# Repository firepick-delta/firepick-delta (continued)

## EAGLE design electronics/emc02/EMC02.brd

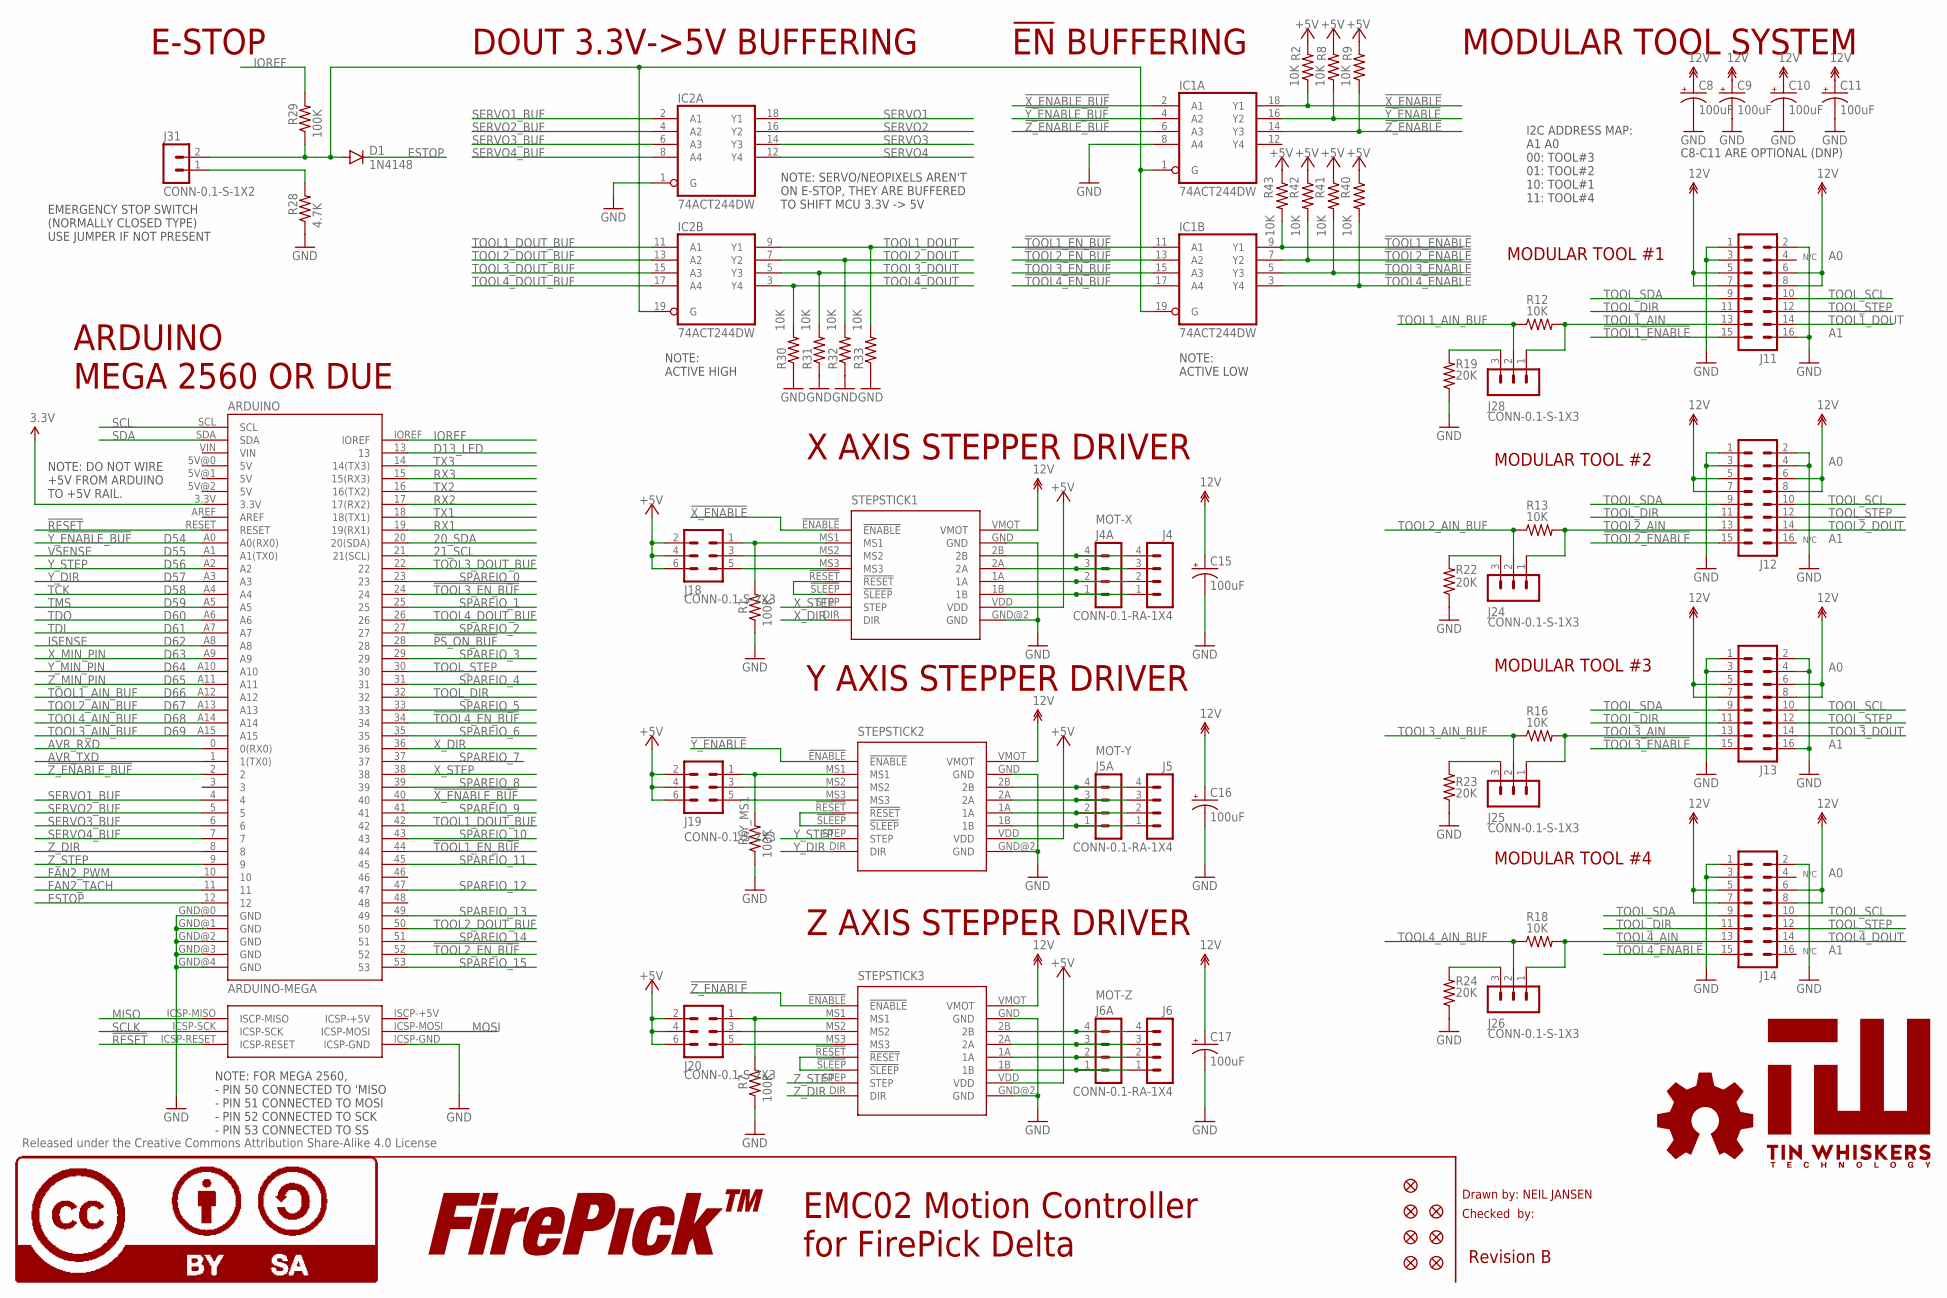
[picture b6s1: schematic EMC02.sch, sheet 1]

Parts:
ARDUINO: ARDUINO-MEGA; PARTNO CONN-0.1-ARD-2560
C8, C9, C10, C11, C15, C16, C17: 100uF; PANASONIC_D; PARTNO 25TXV100M6.3X8
D1: 1N4148; SOD-123; PARTNO 1N4148W-7-F
FID1, FID2, FID3, FID4, FID5, FID6, FID7: FIDUCIAL
IC1, IC2: 74ACT244DW; SO20W; PARTNO 74ACT244SCX
J4, J5, J6: CONN-0.1-RA-1X4; MA04-1; PARTNO CONN-0.1-RA-1X4
J4A: MOT-X; CONN-JST-PH_2.0MM_4PIN-SMT-RA
J5A: MOT-Y; CONN-JST-PH_2.0MM_4PIN-SMT-RA
J6A: MOT-Z; CONN-JST-PH_2.0MM_4PIN-SMT-RA
J11, J12, J13, J14: CONN-RECT-16PIN-2ROW; CONN-RECT-2.54MM-16PIN-2ROW-SMTH; PARTNO PPPC081LFBN-RC
J18, J19, J20: CONN-0.1-S-2X3; MA03-2; PARTNO CONN-0.1-S-2X3
J24, J25, J26, J28: CONN-0.1-S-1X3; MA03-1; PARTNO CONN-0.1-S-1X3
J31: CONN-0.1-S-1X2; MA02-1; PARTNO CONN-0.1-S-1X2
LOGO4: LOGO-FIREPICKLARGE; LOGO-FIREPICK
LOGO5: LOGO-OSHWMEDIUM; LOGO-OSHW-MEDIUM
LOGO6: LOGO-CC-BY-SALARGE; LOGO-CC-BY-SA
R1, R6, R7, R29: 100K; 0805; PARTNO RC0805FR-07100KL
R2, R8, R9, R12, R13, R16, R18, R30, R31, R32, R33, R40, R41, R42, R43: 10K; 0805; PARTNO RC0805FR-0710KL
R19, R22, R23, R24: 20K; 0805; PARTNO RC0805FR-0720KL
R28: 4.7K; 0805; PARTNO RC0805FR-074K7L
STEPSTICK1, STEPSTICK2, STEPSTICK3: STEPSTICK; PARTNO PPPC081LFBN-RC
U$25: TIN-WHISKERSTSTOP; TIN-WHISKERS-TSTOP

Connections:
3.3V: ARDUINO.3.3V; also elsewhere on the board
12V: C8.+, C9.+, C10.+, C11.+, C15.+, C16.+, C17.+, J11.5, J11.6, J11.7, J11.8, J12.5, J12.6, J12.7, J12.8, J13.5, J13.6, J13.7, J13.8, J14.5, J14.6, J14.7, J14.8, STEPSTICK1.VMOT, STEPSTICK2.VMOT, STEPSTICK3.VMOT; also elsewhere on the board
20_SDA: ARDUINO.20 (20(SDA)); also elsewhere on the board
21_SCL: ARDUINO.21 (21(SCL)); also elsewhere on the board
!PS_ON_BUF: ARDUINO.28; also elsewhere on the board
!RESET: ARDUINO.ICSP-RESET, ARDUINO.RESET; also elsewhere on the board
!TOOL1_ENABLE: IC1.9 (Y1), J11.15, R43.2
!TOOL1_EN_BUF: ARDUINO.44, IC1.11 (A1)
!TOOL2_ENABLE: IC1.7 (Y2), J12.15, R42.2
!TOOL2_EN_BUF: ARDUINO.52, IC1.13 (A2)
!TOOL3_ENABLE: IC1.5 (Y3), J13.15, R41.2
!TOOL3_EN_BUF: ARDUINO.24, IC1.15 (A3)
!TOOL4_ENABLE: IC1.3 (Y4), J14.15, R40.2
!TOOL4_EN_BUF: ARDUINO.34, IC1.17 (A4)
!X_ENABLE: IC1.18 (Y1), R2.1, STEPSTICK1.!ENABLE!
!X_ENABLE_BUF: ARDUINO.40, IC1.2 (A1)
!Y_ENABLE: IC1.16 (Y2), R8.1, STEPSTICK2.!ENABLE!
!Y_ENABLE_BUF: ARDUINO.A0 (A0(RX0)), IC1.4 (A2)
!Z_ENABLE: IC1.14 (Y3), R9.1, STEPSTICK3.!ENABLE!
!Z_ENABLE_BUF: ARDUINO.2, IC1.6 (A3)
+5V: J18.2, J18.4, J18.6, J19.2, J19.4, J19.6, J20.2, J20.4, J20.6, R2.2, R8.2, R9.2, R40.1, R41.1, R42.1, R43.1, STEPSTICK1.VDD, STEPSTICK2.VDD, STEPSTICK3.VDD; also elsewhere on the board
AVR_RXD: ARDUINO.0 (0(RX0)); also elsewhere on the board
AVR_TXD: ARDUINO.1 (1(TX0)); also elsewhere on the board
D13_LED: ARDUINO.13; also elsewhere on the board
ESTOP: ARDUINO.12, D1.C
ESTOP_OE: D1.A, IC1.1 (G), IC1.19 (G), IC2.19 (G), J31.2, R29.1
FAN2_PWM: ARDUINO.10; also elsewhere on the board
FAN2_TACH: ARDUINO.11; also elsewhere on the board
GND: ARDUINO.GND@0 (GND), ARDUINO.GND@1 (GND), ARDUINO.GND@2 (GND), ARDUINO.GND@3 (GND), ARDUINO.GND@4 (GND), ARDUINO.ICSP-GND, C8.-, C9.-, C10.-, C11.-, C15.-, C16.-, C17.-, IC1.8 (A4), IC2.1 (G), J11.1, J11.2, J11.3, J11.16, J12.1, J12.2, J12.3, J12.4, J13.1, J13.2, J13.3, J13.4, J13.16, J14.1, J14.2, J14.3, R1.1, R6.1, R7.1, R19.1, R22.1, R23.1, R24.1, R28.1, R30.1, R31.1, R32.1, R33.1, STEPSTICK1.GND, STEPSTICK1.GND@2 (GND), STEPSTICK2.GND, STEPSTICK2.GND@2 (GND), STEPSTICK3.GND, STEPSTICK3.GND@2 (GND); also elsewhere on the board
IOREF: ARDUINO.IOREF, R29.2; also elsewhere on the board
ISENSE: ARDUINO.A8; also elsewhere on the board
MISO: ARDUINO.ICSP-MISO (ISCP-MISO); also elsewhere on the board
MOSI: ARDUINO.ICSP-MOSI; also elsewhere on the board
unnamed: J31.1, R28.2
unnamed: J24.3, R22.2
unnamed: J28.3, R19.2
unnamed: STEPSTICK1.!RESET!, STEPSTICK1.!SLEEP!
unnamed: J25.3, R23.2
unnamed: J26.3, R24.2
unnamed: STEPSTICK2.!RESET!, STEPSTICK2.!SLEEP!
unnamed: STEPSTICK3.!RESET!, STEPSTICK3.!SLEEP!
RX1: ARDUINO.19 (19(RX1)); also elsewhere on the board
RX2: ARDUINO.17 (17(RX2)); also elsewhere on the board
RX3: ARDUINO.15 (15(RX3)); also elsewhere on the board
SCL: ARDUINO.SCL; also elsewhere on the board
SCLK: ARDUINO.ICSP-SCK; also elsewhere on the board
SDA: ARDUINO.SDA; also elsewhere on the board
SERVO1: IC2.18 (Y1); also elsewhere on the board
SERVO1_BUF: ARDUINO.4, IC2.2 (A1)
SERVO2: IC2.16 (Y2); also elsewhere on the board
SERVO2_BUF: ARDUINO.5, IC2.4 (A2)
SERVO3: IC2.14 (Y3); also elsewhere on the board
SERVO3_BUF: ARDUINO.6, IC2.6 (A3)
SERVO4: IC2.12 (Y4); also elsewhere on the board
SERVO4_BUF: ARDUINO.7, IC2.8 (A4)
SPAREIO_0: ARDUINO.23; also elsewhere on the board
SPAREIO_1: ARDUINO.25; also elsewhere on the board
SPAREIO_2: ARDUINO.27; also elsewhere on the board
SPAREIO_3: ARDUINO.29; also elsewhere on the board
SPAREIO_4: ARDUINO.31; also elsewhere on the board
SPAREIO_5: ARDUINO.33; also elsewhere on the board
SPAREIO_6: ARDUINO.35; also elsewhere on the board
SPAREIO_7: ARDUINO.37; also elsewhere on the board
SPAREIO_8: ARDUINO.39; also elsewhere on the board
SPAREIO_9: ARDUINO.41; also elsewhere on the board
SPAREIO_10: ARDUINO.43; also elsewhere on the board
SPAREIO_11: ARDUINO.45; also elsewhere on the board
SPAREIO_12: ARDUINO.47; also elsewhere on the board
SPAREIO_13: ARDUINO.49; also elsewhere on the board
SPAREIO_14: ARDUINO.51; also elsewhere on the board
SPAREIO_15: ARDUINO.53; also elsewhere on the board
TCK: ARDUINO.A4; also elsewhere on the board
TDI: ARDUINO.A7; also elsewhere on the board
TDO: ARDUINO.A6; also elsewhere on the board
TMS: ARDUINO.A5; also elsewhere on the board
TOOL1_AIN: J11.13, J28.1, R12.2
TOOL1_AIN_BUF: ARDUINO.A12, J28.2, R12.1
TOOL1_DOUT: IC2.9 (Y1), J11.14, R33.2
TOOL1_DOUT_BUF: ARDUINO.42, IC2.11 (A1)
TOOL2_AIN: J12.13, J24.1, R13.2
TOOL2_AIN_BUF: ARDUINO.A13, J24.2, R13.1
TOOL2_DOUT: IC2.7 (Y2), J12.14, R32.2
TOOL2_DOUT_BUF: ARDUINO.50, IC2.13 (A2)
TOOL3_AIN: J13.13, J25.1, R16.2
TOOL3_AIN_BUF: ARDUINO.A15, J25.2, R16.1
TOOL3_DOUT: IC2.5 (Y3), J13.14, R31.2
TOOL3_DOUT_BUF: ARDUINO.22, IC2.15 (A3)
TOOL4_AIN: J14.13, J26.1, R18.2
TOOL4_AIN_BUF: ARDUINO.A14, J26.2, R18.1
TOOL4_DOUT: IC2.3 (Y4), J14.14, R30.2
TOOL4_DOUT_BUF: ARDUINO.26, IC2.17 (A4)
TOOL_DIR: ARDUINO.32, J11.11, J12.11, J13.11, J14.11
TOOL_SCL: J11.10, J12.10, J13.10, J14.10; also elsewhere on the board
TOOL_SDA: J11.9, J12.9, J13.9, J14.9; also elsewhere on the board
TOOL_STEP: ARDUINO.30, J11.12, J12.12, J13.12, J14.12
TX1: ARDUINO.18 (18(TX1)); also elsewhere on the board
TX2: ARDUINO.16 (16(TX2)); also elsewhere on the board
TX3: ARDUINO.14 (14(TX3)); also elsewhere on the board
VSENSE: ARDUINO.A1 (A1(TX0)); also elsewhere on the board
X1A: J4.2, J4A.2, STEPSTICK1.1A
X1B: J4.1, J4A.1, STEPSTICK1.1B
X2A: J4.3, J4A.3, STEPSTICK1.2A
X2B: J4.4, J4A.4, STEPSTICK1.2B
X_DIR: ARDUINO.36, STEPSTICK1.DIR
X_MIN_PIN: ARDUINO.A9; also elsewhere on the board
X_MS1: J18.1, R1.2, STEPSTICK1.MS1
X_MS2: J18.3, STEPSTICK1.MS2
X_MS3: J18.5, STEPSTICK1.MS3
X_STEP: ARDUINO.38, STEPSTICK1.STEP
Y1A: J5.2, J5A.2, STEPSTICK2.1A
Y1B: J5.1, J5A.1, STEPSTICK2.1B
Y2A: J5.3, J5A.3, STEPSTICK2.2A
Y2B: J5.4, J5A.4, STEPSTICK2.2B
Y_DIR: ARDUINO.A3, STEPSTICK2.DIR
Y_MIN_PIN: ARDUINO.A10; also elsewhere on the board
Y_MS1: J19.1, R6.2, STEPSTICK2.MS1
Y_MS2: J19.3, STEPSTICK2.MS2
Y_MS3: J19.5, STEPSTICK2.MS3
Y_STEP: ARDUINO.A2, STEPSTICK2.STEP
Z1A: J6.2, J6A.2, STEPSTICK3.1A
Z1B: J6.1, J6A.1, STEPSTICK3.1B
Z2A: J6.3, J6A.3, STEPSTICK3.2A
Z2B: J6.4, J6A.4, STEPSTICK3.2B
Z_DIR: ARDUINO.8, STEPSTICK3.DIR
Z_MIN_PIN: ARDUINO.A11; also elsewhere on the board
Z_MS1: J20.1, R7.2, STEPSTICK3.MS1
Z_MS2: J20.3, STEPSTICK3.MS2
Z_MS3: J20.5, STEPSTICK3.MS3
Z_STEP: ARDUINO.9, STEPSTICK3.STEP

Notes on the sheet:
I2C ADDRESS MAP: A1 A0 00: TOOL#3 01: TOOL#2 10: TOOL#1 11: TOOL#4
MODULAR TOOL #4
MODULAR TOOL #3
MODULAR TOOL #2
MODULAR TOOL #1
Drawn by: NEIL JANSEN
Checked by:
Revision B
EMC02 Motion Controller for FirePick Delta
ARDUINO MEGA 2560 OR DUE
X AXIS STEPPER DRIVER
N/C
Y AXIS STEPPER DRIVER
Z AXIS STEPPER DRIVER
Released under the Creative Commons Attribution Share-Alike 4.0 License
D54
D55
D56
D57
D58
D59
D60
D61
D62
D63
D64
D65
D66
D67
D68
D69
NOTE: DO NOT WIRE +5V FROM ARDUINO TO +5V RAIL.
MODULAR TOOL SYSTEM
DOUT 3.3V->5V BUFFERING
EMERGENCY STOP SWITCH (NORMALLY CLOSED TYPE) USE JUMPER IF NOT PRESENT
E-STOP
!EN! BUFFERING
NOTE: ACTIVE HIGH
NOTE: ACTIVE LOW
NOTE: SERVO/NEOPIXELS AREN'T ON E-STOP, THEY ARE BUFFERED TO SHIFT MCU 3.3V -> 5V

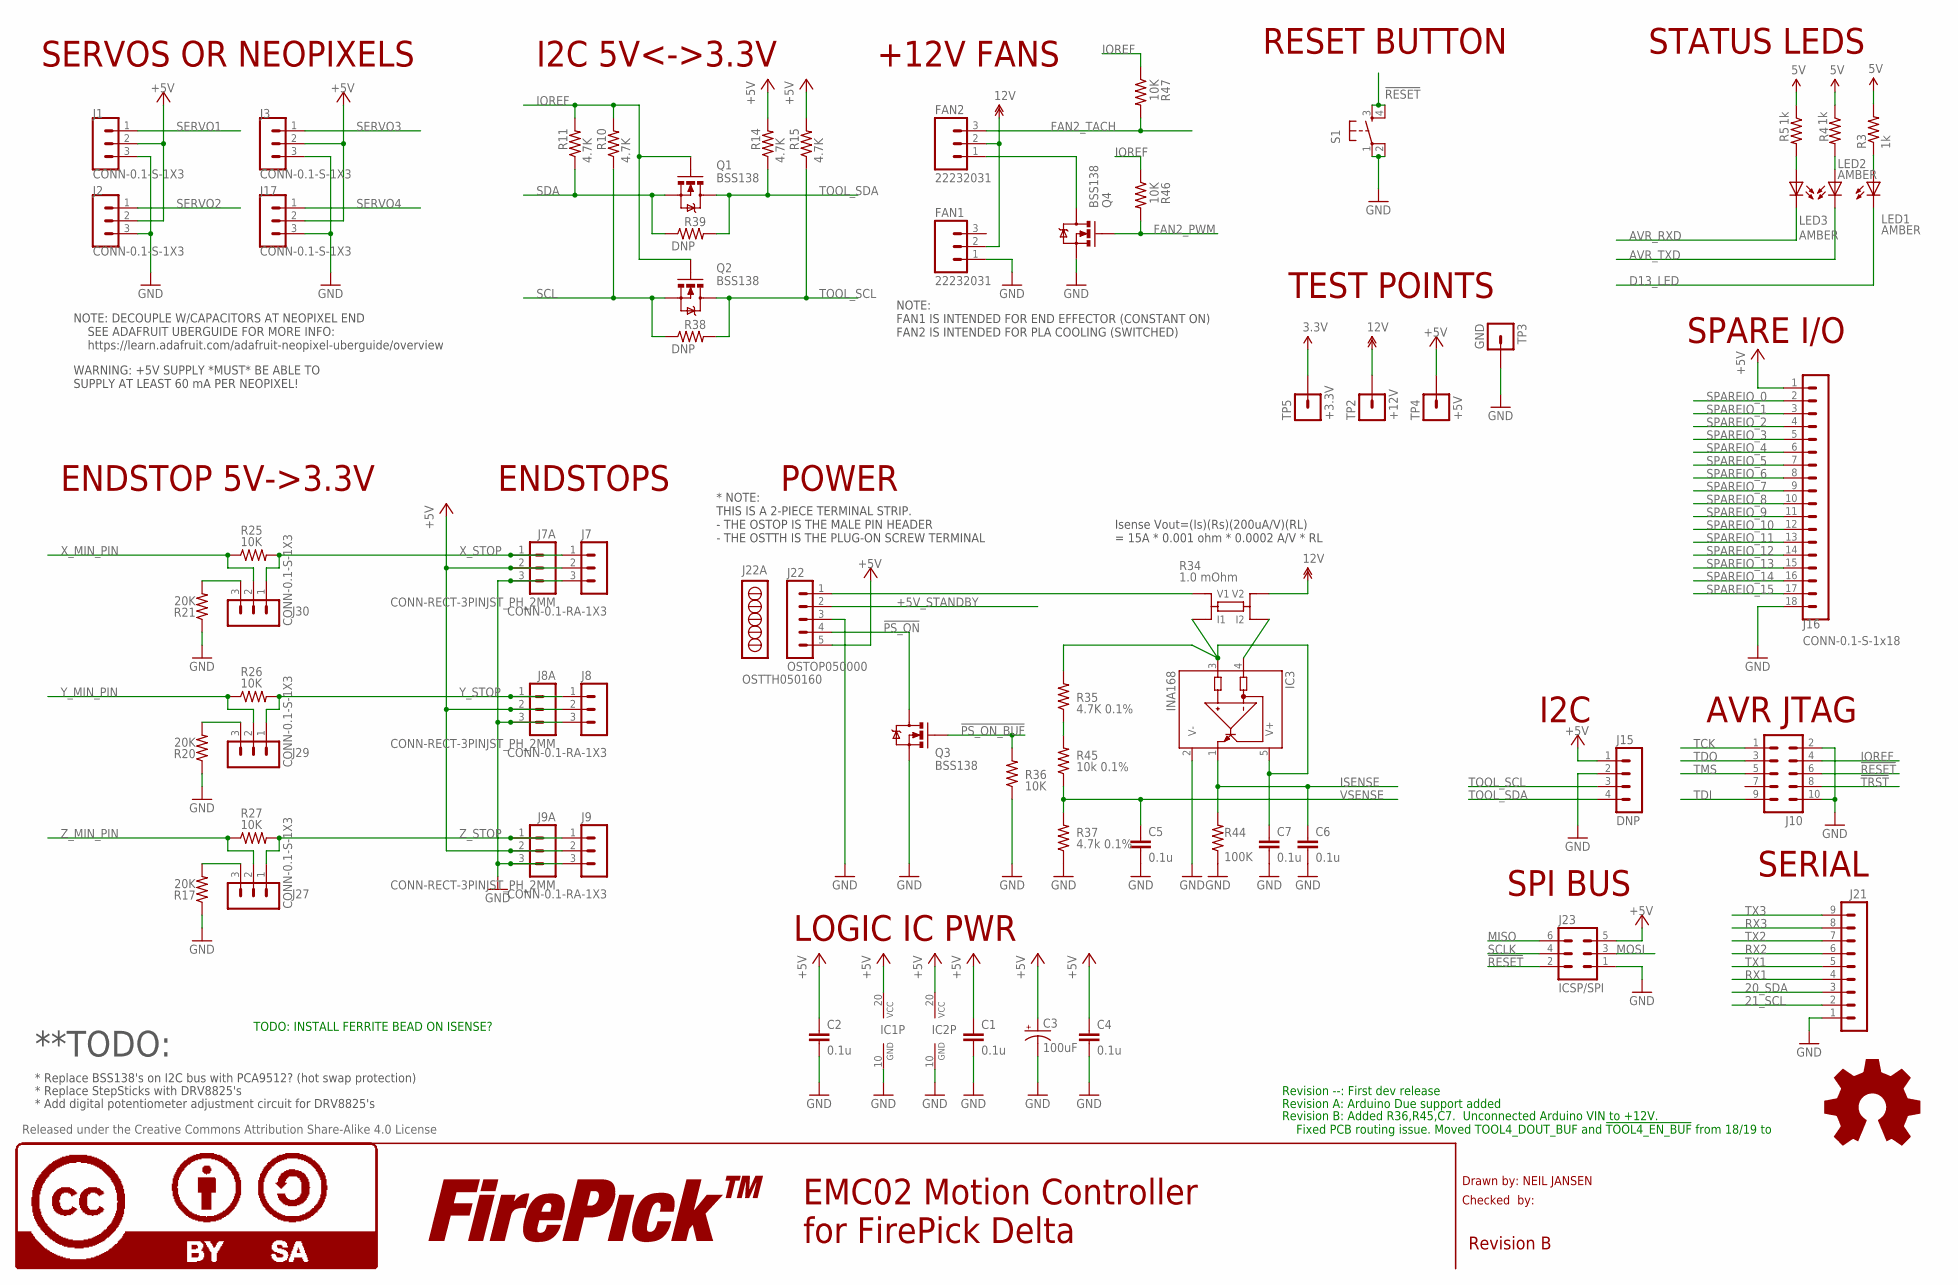
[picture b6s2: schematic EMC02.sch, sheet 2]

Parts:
C1, C2, C4, C5, C6, C7: 0.1u; 0805; PARTNO CC0805ZRY5V9BB104
C3: 100uF; PANASONIC_D; PARTNO 25TXV100M6.3X8
FAN1, FAN2: 22232031; MOLEX-1X3_LOCK; PARTNO 22232031
IC1, IC2: 74ACT244DW; SO20W; PARTNO 74ACT244SCX
IC3: INA168; SOT23-5; PARTNO INA168NA/3K
J1, J2, J3, J17, J27, J29, J30: CONN-0.1-S-1X3; MA03-1; PARTNO CONN-0.1-S-1X3
J7, J8, J9: CONN-0.1-RA-1X3; MA03-1; PARTNO CONN-0.1-RA-1X3
J7A, J8A, J9A: CONN-RECT-3PINJST_PH_2MM; CONN-JST_PH-2.0MM-3PIN-SMT-RA
J10: MA05-2
J15: DNP; MA04-1
J16: CONN-0.1-S-1x18; MA18-1
J21: MA09-1
J22: OSTOP050000; CONN-OSTOP050000; PARTNO OSTOP240000
J22A: OSTTH050160; CONN-OSTTH050160; PARTNO OSTTH050160
J23: ICSP/SPI; MA03-2
LED1, LED2, LED3: AMBER; LED-1206-NO_SILK; PARTNO LTST-C150AKT
LOGO1: LOGO-FIREPICKLARGE; LOGO-FIREPICK
LOGO2: LOGO-OSHWMEDIUM; LOGO-OSHW-MEDIUM
LOGO3: LOGO-CC-BY-SALARGE; LOGO-CC-BY-SA
Q1, Q2, Q3, Q4: BSS138; SOT23; PARTNO BSS138
R3, R4, R5: 1k; 0805; PARTNO RC0805FR-071KL
R10, R11, R14, R15: 4.7K; 0805; PARTNO RC0805FR-074K7L
R17, R20, R21: 20K; 0805; PARTNO RC0805FR-0720KL
R25, R26, R27, R36, R46, R47: 10K; 0805; PARTNO RC0805FR-0710KL
R34: 1.0 mOhm; CHIP-1224-KELVIN; PARTNO LVK25R001FER
R35: 4.7K 0.1%; 0805; PARTNO *
R37: 4.7k 0.1%; 0805; PARTNO *
R38, R39: DNP; 0805
R44: 100K; 0805; PARTNO *
R45: 10k 0.1%; 0805; PARTNO *
S1: TAC_SWITCHSMD; TACTILE_SWITCH_SMD; PARTNO SWITCH TACTILE SPST-NO 0.05A 12V
TP2: +12V; CON-TESTPOINT
TP3: GND; CON-TESTPOINT
TP4: +5V; CON-TESTPOINT
TP5: +3.3V; CON-TESTPOINT

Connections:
3.3V: TP5.1; also elsewhere on the board
12V: FAN1.2, FAN2.2, R34.V2, TP2.1; also elsewhere on the board
20_SDA: J21.3; also elsewhere on the board
21_SCL: J21.2; also elsewhere on the board
!PS_ON: J22.4, Q3.3 (D)
!PS_ON_BUF: Q3.1 (G), R36.2; also elsewhere on the board
!RESET: J10.6, J23.2, S1.3, S1.4; also elsewhere on the board
!TRST: J10.8
+5V: C1.1, C2.1, C3.+, C4.1, IC1.20 (VCC), IC2.20 (VCC), J1.2, J2.2, J3.2, J7.2, J7A.2, J8.2, J8A.2, J9.2, J9A.2, J15.1, J16.1, J17.2, J22.5, J23.5, R3.2, R4.1, R5.1, R14.2, R15.2, TP4.1; also elsewhere on the board
+5V_STANDBY: J22.2
AVR_RXD: LED3.C; also elsewhere on the board
AVR_TXD: LED2.C; also elsewhere on the board
D13_LED: LED1.C; also elsewhere on the board
FAN2_PWM: Q4.1 (G), R46.2; also elsewhere on the board
FAN2_TACH: FAN2.3, R47.2; also elsewhere on the board
GND: C1.2, C2.2, C3.-, C4.2, C5.2, C6.2, C7.2, FAN1.1, IC1.10 (GND), IC2.10 (GND), IC3.2 (V-), J1.3, J2.3, J3.3, J7.3, J7A.3, J8.3, J8A.3, J9.3, J9A.3, J10.2, J10.10, J15.2, J16.18, J17.3, J21.1, J22.3, J23.1, Q3.2 (S), Q4.2 (S), R17.1, R20.1, R21.1, R36.1, R37.1, R44.1, S1.1, S1.2, TP3.1; also elsewhere on the board
IOREF: J10.4, Q1.1 (G), Q2.1 (G), R10.2, R11.2, R46.1, R47.1; also elsewhere on the board
ISENSE: C6.1, IC3.1 (OUT), R44.2; also elsewhere on the board
MISO: J23.6; also elsewhere on the board
MOSI: J23.3; also elsewhere on the board
unnamed: R35.1, R45.2
unnamed: FAN2.1, Q4.3 (D)
unnamed: J22.1, R34.V1
unnamed: LED1.A, R3.1
unnamed: J27.3, R17.2
unnamed: J29.3, R20.2
unnamed: J30.3, R21.2
unnamed: C7.1, IC3.3 (IN+), IC3.5 (V+), R34.I1, R35.2
unnamed: IC3.4 (IN-), R34.I2
unnamed: LED2.A, R4.2
unnamed: LED3.A, R5.2
RX1: J21.4; also elsewhere on the board
RX2: J21.6; also elsewhere on the board
RX3: J21.8; also elsewhere on the board
SCL: Q2.2 (S), R10.1, R38.1; also elsewhere on the board
SCLK: J23.4; also elsewhere on the board
SDA: Q1.2 (S), R11.1, R39.1; also elsewhere on the board
SERVO1: J1.1; also elsewhere on the board
SERVO2: J2.1; also elsewhere on the board
SERVO3: J3.1; also elsewhere on the board
SERVO4: J17.1; also elsewhere on the board
SPAREIO_0: J16.2; also elsewhere on the board
SPAREIO_1: J16.3; also elsewhere on the board
SPAREIO_2: J16.4; also elsewhere on the board
SPAREIO_3: J16.5; also elsewhere on the board
SPAREIO_4: J16.6; also elsewhere on the board
SPAREIO_5: J16.7; also elsewhere on the board
SPAREIO_6: J16.8; also elsewhere on the board
SPAREIO_7: J16.9; also elsewhere on the board
SPAREIO_8: J16.10; also elsewhere on the board
SPAREIO_9: J16.11; also elsewhere on the board
SPAREIO_10: J16.12; also elsewhere on the board
SPAREIO_11: J16.13; also elsewhere on the board
SPAREIO_12: J16.14; also elsewhere on the board
SPAREIO_13: J16.15; also elsewhere on the board
SPAREIO_14: J16.16; also elsewhere on the board
SPAREIO_15: J16.17; also elsewhere on the board
TCK: J10.1; also elsewhere on the board
TDI: J10.9; also elsewhere on the board
TDO: J10.3; also elsewhere on the board
TMS: J10.5; also elsewhere on the board
TOOL_SCL: J15.3, Q2.3 (D), R15.1, R38.2; also elsewhere on the board
TOOL_SDA: J15.4, Q1.3 (D), R14.1, R39.2; also elsewhere on the board
TX1: J21.5; also elsewhere on the board
TX2: J21.7; also elsewhere on the board
TX3: J21.9; also elsewhere on the board
VSENSE: C5.1, R37.2, R45.1; also elsewhere on the board
X_MIN_PIN: J30.2, R25.1; also elsewhere on the board
X_STOP: J7.1, J7A.1, J30.1, R25.2
Y_MIN_PIN: J29.2, R26.1; also elsewhere on the board
Y_STOP: J8.1, J8A.1, J29.1, R26.2
Z_MIN_PIN: J27.2, R27.1; also elsewhere on the board
Z_STOP: J9.1, J9A.1, J27.1, R27.2

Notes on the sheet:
Drawn by: NEIL JANSEN
Checked by:
Revision B
EMC02 Motion Controller for FirePick Delta
Released under the Creative Commons Attribution Share-Alike 4.0 License
**TODO:
* Replace StepSticks with DRV8825's
* Add digital potentiometer adjustment circuit for DRV8825's
* Replace BSS138's on I2C bus with PCA9512? (hot swap protection)
SPI BUS
I2C
TEST POINTS
AVR JTAG
WARNING: +5V SUPPLY *MUST* BE ABLE TO SUPPLY AT LEAST 60 mA PER NEOPIXEL!
+12V FANS
SPARE I/O
SERVOS OR NEOPIXELS
RESET BUTTON
STATUS LEDS
ENDSTOP 5V->3.3V
ENDSTOPS
I2C 5V<->3.3V
LOGIC IC PWR
POWER
Revision --: First dev release
Revision A: Arduino Due support added
NOTE: DECOUPLE W/CAPACITORS AT NEOPIXEL END SEE ADAFRUIT UBERGUIDE FOR MORE INFO: https://learn.adafruit.com/adafruit-neopixel-uberguide/overview
* NOTE: THIS IS A 2-PIECE TERMINAL STRIP. - THE OSTOP IS THE MALE PIN HEADER - THE OSTTH IS THE PLUG-ON SCREW TERMINAL
Isense Vout=(Is)(Rs)(200uA/V)(RL) = 15A * 0.001 ohm * 0.0002 A/V * RL
Revision B: Added R36,R45,C7. Unconnected Arduino VIN to +12V. Fixed PCB routing issue. Moved TOOL4_DOUT_BUF and !TOOL4_EN_BUF! from 18/19 to
TODO: INSTALL FERRITE BEAD ON ISENSE?
SERIAL
NOTE: FAN1 IS INTENDED FOR END EFFECTOR (CONSTANT ON) FAN2 IS INTENDED FOR PLA COOLING (SWITCHED)

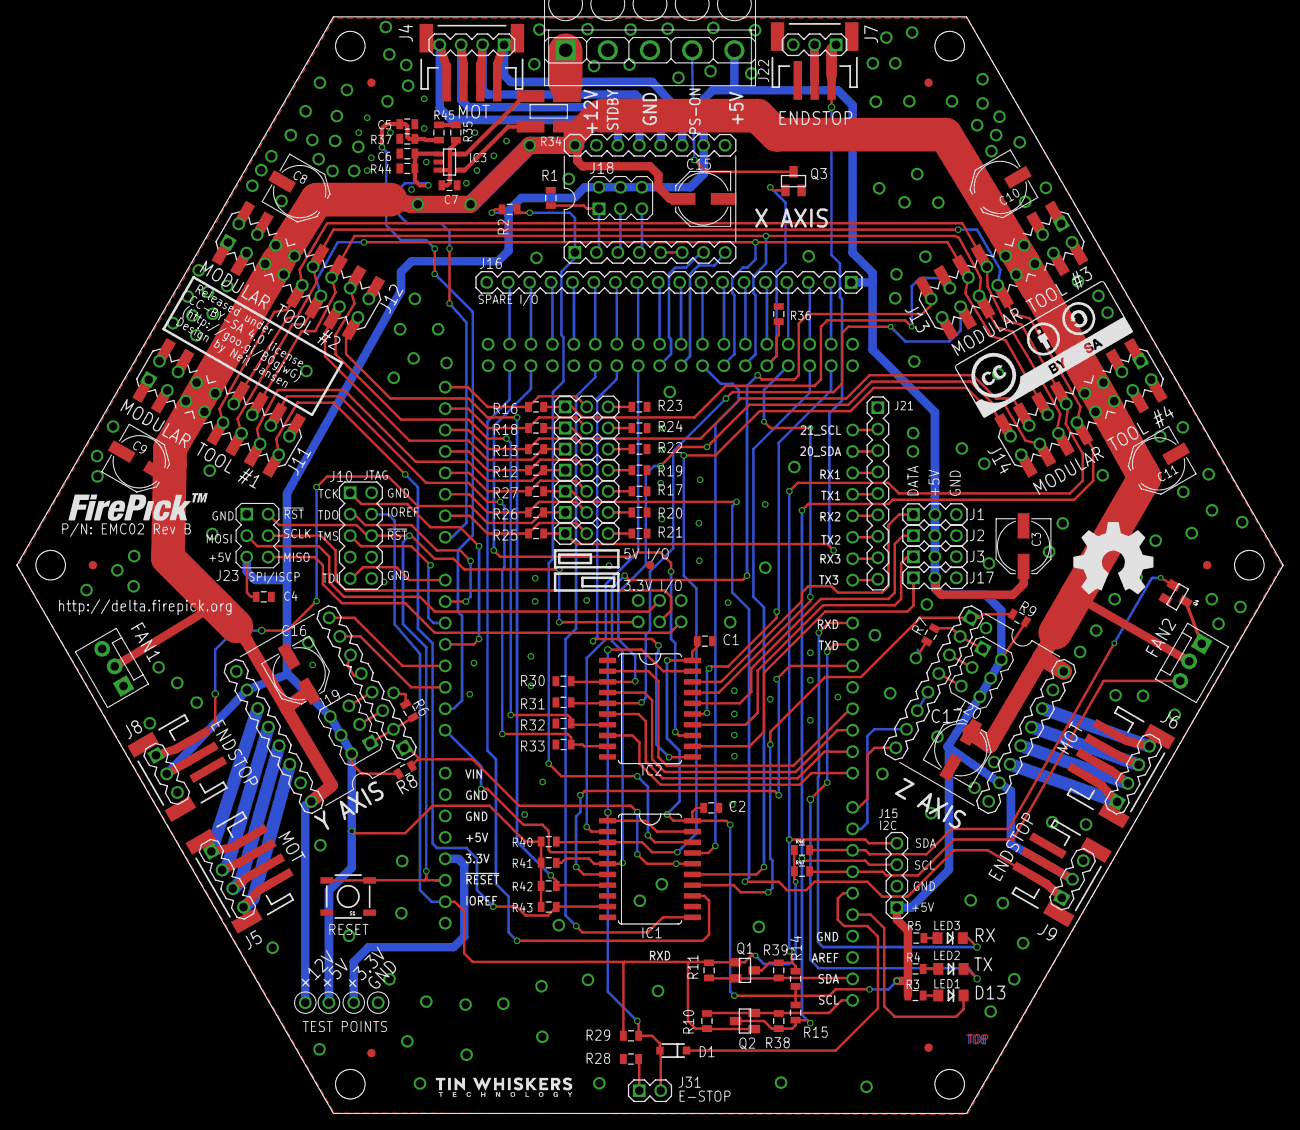
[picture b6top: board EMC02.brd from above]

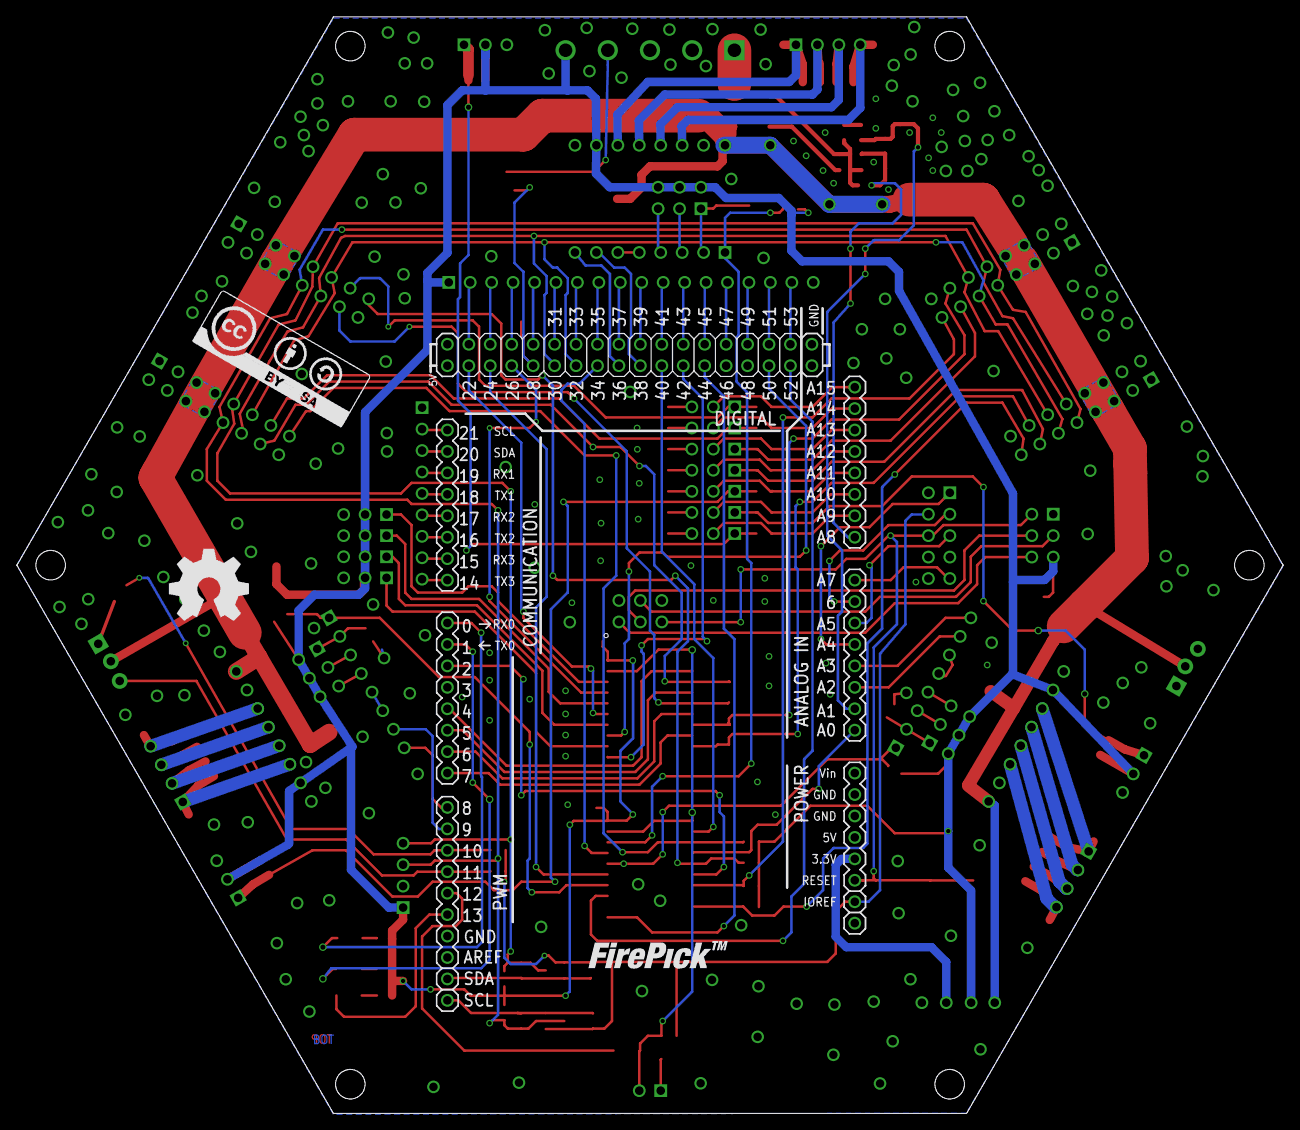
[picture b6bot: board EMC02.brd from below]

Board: 2 copper layers, 150.0 x 129.9 mm, 135 parts (4 on the bottom side), 144 nets.

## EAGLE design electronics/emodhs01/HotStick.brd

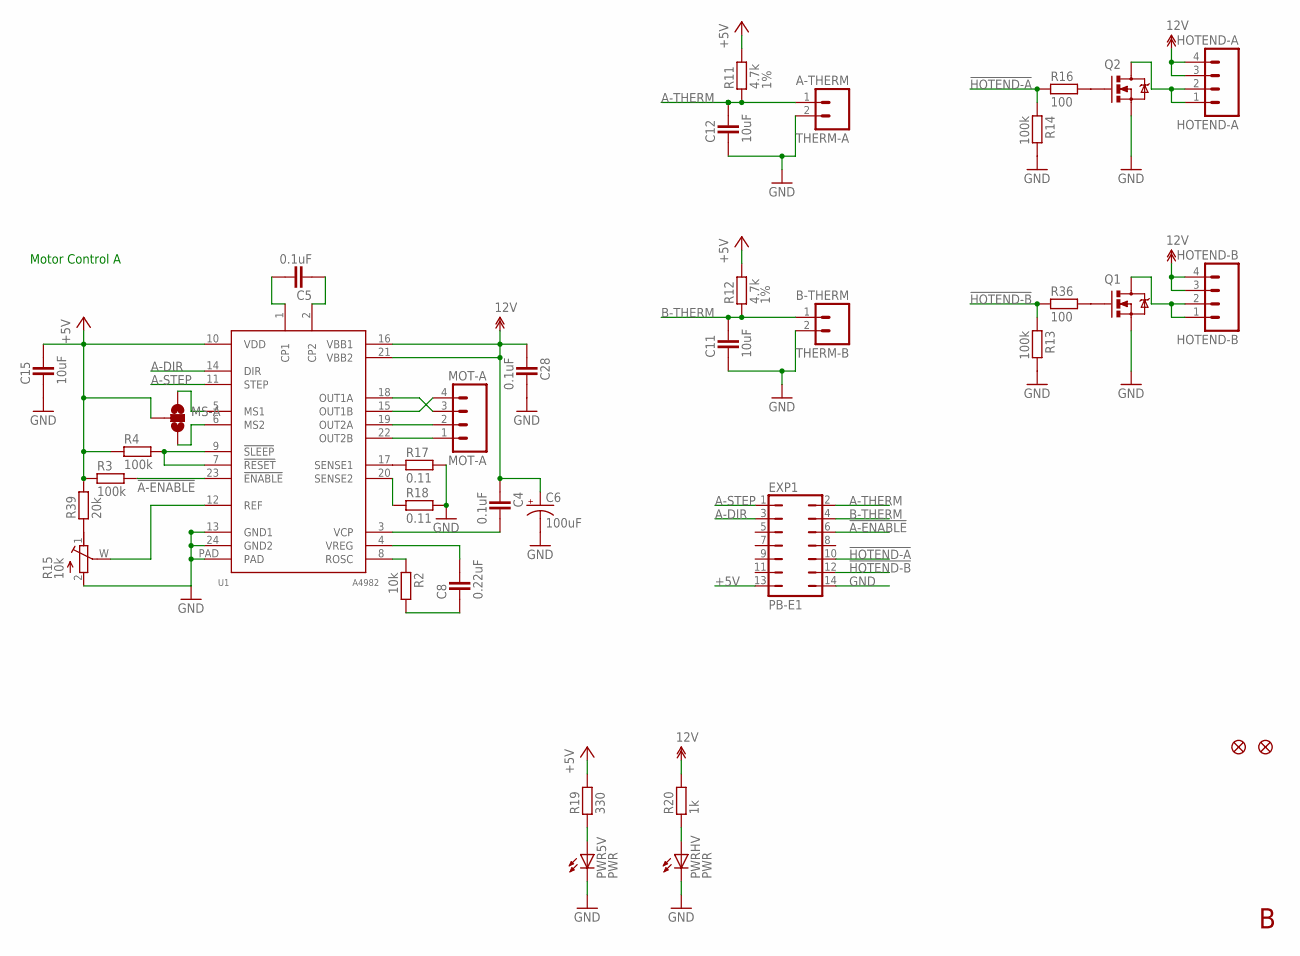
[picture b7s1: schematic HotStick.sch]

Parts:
C4, C5, C28: 0.1uF; CAPC2012X145AN
C6: 100uF; PANASONIC_D
C8: 0.22uF; CAPC2012X145AN
C11, C12, C15: 10uF; CAPC2012X145AN
EXP1: PB-E1; JP7Q
HOTEND-A: HOTEND-A; MOLEX-1X4
HOTEND-B: HOTEND-B; MOLEX-1X4
JP1, JP2: FIDUCIAL1X2.5; FIDUCIAL-1X2.5
MOT-A: MOT-A; MOLEX-1X4
MS-A: SOLDERJUMPER_2WAYCONNECTED; SJ_3_CONNECTED
PWR5V: PWR; CHIP-LED0805
PWRHV: PWR; CHIP-LED0805
Q1, Q2: MOSFET-NCHANNELPTH2; TO220V
R2: 10k; RESC2012X70N
R3, R4, R13, R14: 100k; RESC2012X70N
R11, R12: 4.7k; RESC2012X70N; TOLERANCE 1%
R15: 10k; RTRIM-ST4ETB
R16, R36: 100; RESC2012X70N
R17, R18: 0.11; RESC2012X70N
R19: 330; RESC2012X70N
R20: 1k; RESC2012X70N
R39: 20k; RESC2012X70N
THERM-A: A-THERM; 1X02
THERM-B: B-THERM; 1X02
U1: A4982; TSSOP-24

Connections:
12V: C4.1, C6.+, C28.1, HOTEND-A.3, HOTEND-A.4, HOTEND-B.3, HOTEND-B.4, R20.2, U1.16 (VBB1), U1.21 (VBB2)
!A-ENABLE: EXP1.6, R3.2, U1.23 (!ENABLE)
!HOTEND-A: EXP1.10, R14.1, R16.1
!HOTEND-B: EXP1.12, R13.1, R36.1
+5V: C15.2, EXP1.13, MS-A.2, R3.1, R4.1, R11.2, R12.2, R19.2, R39.2, U1.10 (VDD)
A-DIR: EXP1.3, U1.14 (DIR)
A-STEP: EXP1.1, U1.11 (STEP)
A-THERM: C12.2, EXP1.2, R11.1, THERM-A.1
B-THERM: C11.2, EXP1.4, R12.1, THERM-B.1
GND: C6.-, C11.1, C12.1, C15.1, C28.2, EXP1.14, PWR5V.C, PWRHV.C, Q1.3 (S), Q2.3 (S), R13.2, R14.2, R15.2 (E), R17.2, R18.2, THERM-A.2, THERM-B.2, U1.13 (GND1), U1.24 (GND2), U1.PAD
HOTENDA-GND: HOTEND-A.1, HOTEND-A.2, Q2.2 (D)
HOTENDB-GND: HOTEND-B.1, HOTEND-B.2, Q1.2 (D)
unnamed: MOT-A.3, U1.18 (OUT1A)
unnamed: C5.2, U1.1 (CP1)
unnamed: C5.1, U1.2 (CP2)
unnamed: R2.1, U1.8 (ROSC)
unnamed: R17.1, U1.17 (SENSE1)
unnamed: R18.1, U1.20 (SENSE2)
unnamed: C4.2, U1.3 (VCP)
unnamed: MOT-A.4, U1.15 (OUT1B)
unnamed: R15.W (S), U1.12 (REF)
unnamed: C8.2, U1.4 (VREG)
unnamed: MOT-A.2, U1.19 (OUT2A)
unnamed: R4.2, U1.7 (!RESET), U1.9 (!SLEEP)
unnamed: MOT-A.1, U1.22 (OUT2B)
unnamed: MS-A.1, U1.5 (MS1)
unnamed: MS-A.3, U1.6 (MS2)
unnamed: Q2.1 (G), R16.2
unnamed: PWR5V.A, R19.1
unnamed: PWRHV.A, R20.1
unnamed: C8.1, R2.2
unnamed: R15.1 (A), R39.1
unnamed: Q1.1 (G), R36.2

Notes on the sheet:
Motor Control A

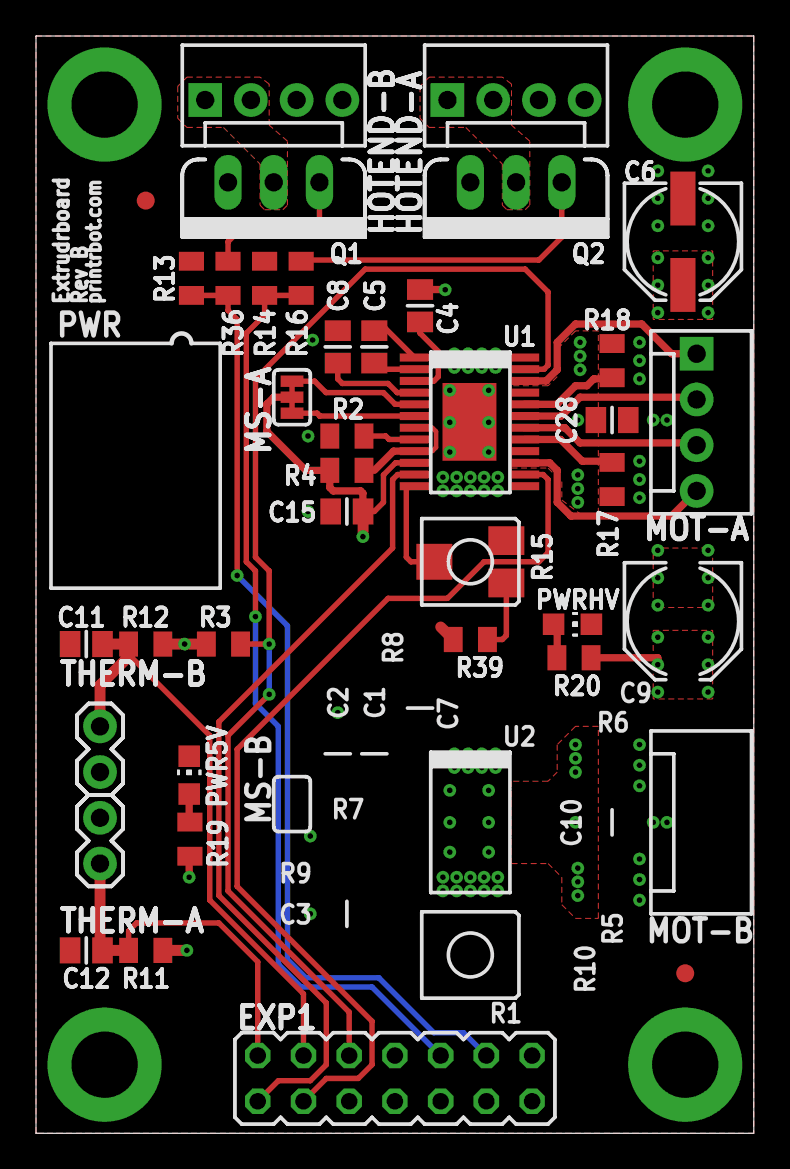
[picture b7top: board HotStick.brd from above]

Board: 4 copper layers, 39.9 x 61.0 mm, 37 parts (0 on the bottom side), 33 nets.
